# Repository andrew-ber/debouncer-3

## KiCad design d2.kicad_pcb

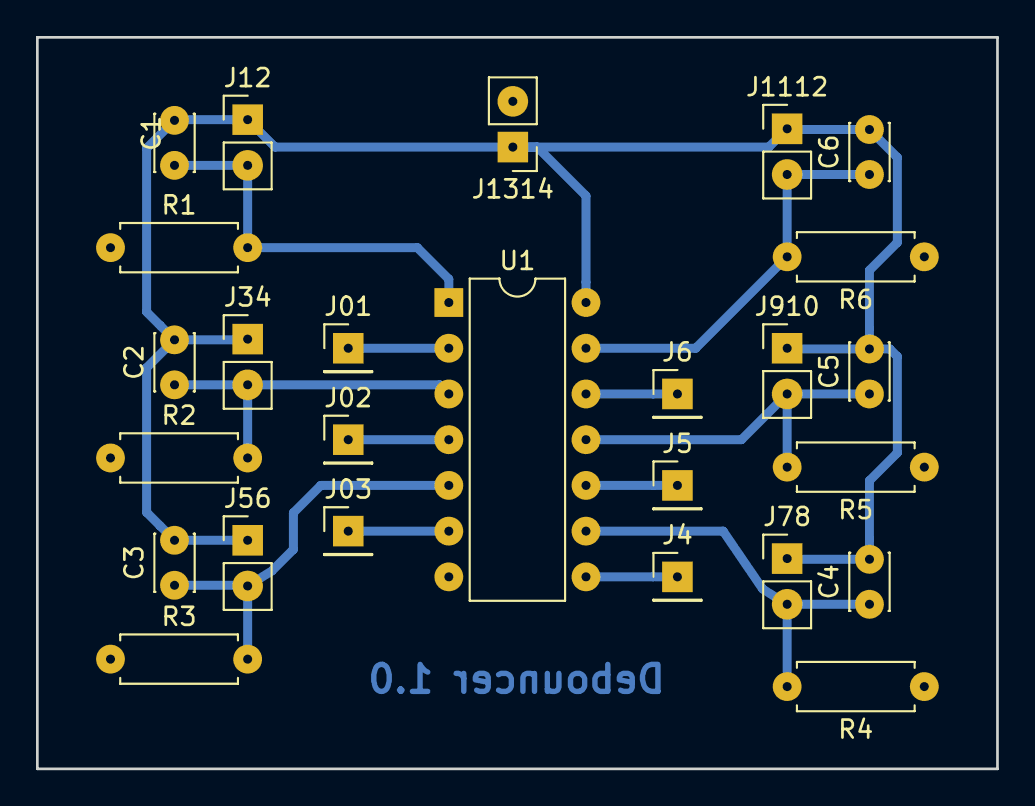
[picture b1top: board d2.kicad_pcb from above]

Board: 2 copper layers, 53.3 x 40.6 mm, 26 parts (0 on the bottom side), 14 nets.

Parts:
C1, C2, C3, C4, C5, C6: C; C_Disc_D3.0mm_W2.0mm_P2.50mm
J01, J02, J03, J4, J5, J6: Conn_01x01_Male; PinHeader_1x01_P2.54mm_Vertical
J12, J34, J56, J78, J910, J1112, J1314: Conn_01x02_Male; PinHeader_1x02_P2.54mm_Vertical
R1, R2: R100K; R_Axial_DIN0207_L6.3mm_D2.5mm_P7.62mm_Horizontal
R3, R4, R5, R6: R; R_Axial_DIN0207_L6.3mm_D2.5mm_P7.62mm_Horizontal
U1: 74HC14; DIP-14_W7.62mm

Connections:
GND: J1314.2, R1.1, R2.1, R3.1, R4.1, R5.1, R6.1, U1.7
unnamed: C1.1, J12.2, R1.2, U1.1
unnamed: C2.1, J34.2, R2.2, U1.3
unnamed: C3.1, J56.2, R3.2, U1.5
unnamed: C4.1, J78.2, R4.2, U1.9
unnamed: C5.1, J910.2, R5.2, U1.11
unnamed: C6.1, J1112.2, R6.2, U1.13
unnamed: J01.1, U1.2
unnamed: J02.1, U1.4
unnamed: J03.1, U1.6
unnamed: J4.1, U1.8
unnamed: J5.1, U1.10
unnamed: J6.1, U1.12
VCC: C1.2, C2.2, C3.2, C4.2, C5.2, C6.2, J12.1, J34.1, J56.1, J78.1, J910.1, J1112.1, J1314.1, U1.14

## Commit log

2018-10-15 init
